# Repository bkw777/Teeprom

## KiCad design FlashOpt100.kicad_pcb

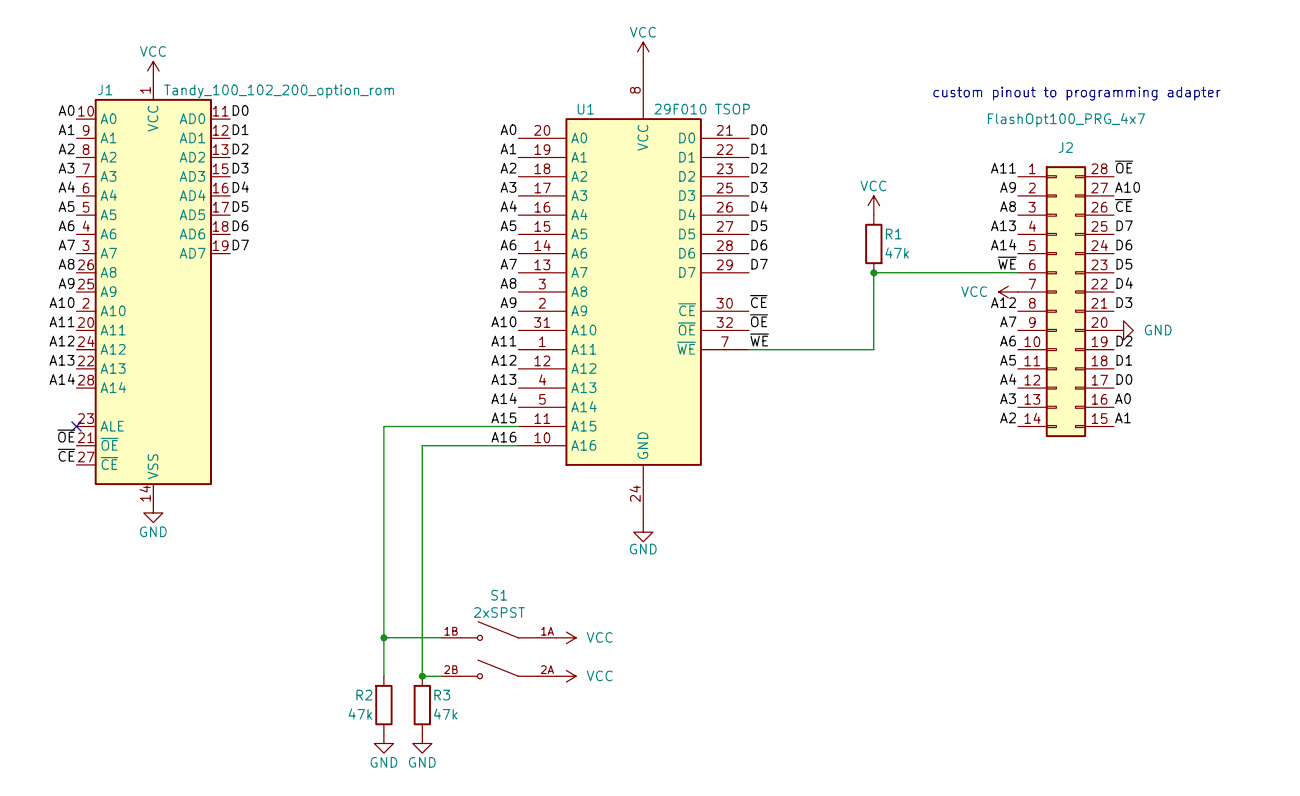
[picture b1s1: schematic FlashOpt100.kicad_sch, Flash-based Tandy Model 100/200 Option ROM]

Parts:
J1: Tandy_100_102_200_option_rom; Molex78802_PCB_28
J2: FlashOpt100_PRG_4x7; FlashOpt100_PRG_4x7_female_offset
R1, R2, R3: 47k; R_0805
S1: 2xSPST; SW_DS05-127-2-02BK-SMT-TR
U1: 29F010 TSOP; TSOP32-14mm

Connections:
/A0: J1.10 (A0), J2.16, U1.20 (A0)
/A1: J1.9 (A1), J2.15, U1.19 (A1)
/A2: J1.8 (A2), J2.14, U1.18 (A2)
/A3: J1.7 (A3), J2.13, U1.17 (A3)
/A4: J1.6 (A4), J2.12, U1.16 (A4)
/A5: J1.5 (A5), J2.11, U1.15 (A5)
/A6: J1.4 (A6), J2.10, U1.14 (A6)
/A7: J1.3 (A7), J2.9, U1.13 (A7)
/A8: J1.26 (A8), J2.3, U1.3 (A8)
/A9: J1.25 (A9), J2.2, U1.2 (A9)
/A10: J1.2 (A10), J2.27, U1.31 (A10)
/A11: J1.20 (A11), J2.1, U1.1 (A11)
/A12: J1.24 (A12), J2.8, U1.12 (A12)
/A13: J1.22 (A13), J2.4, U1.4 (A13)
/A14: J1.28 (A14), J2.5, U1.5 (A14)
/A15: R2.2, S1.1B, U1.11 (A15)
/A16: R3.2, S1.2B, U1.10 (A16)
/D0: J1.11 (AD0), J2.17, U1.21 (D0)
/D1: J1.12 (AD1), J2.18, U1.22 (D1)
/D2: J1.13 (AD2), J2.19, U1.23 (D2)
/D3: J1.15 (AD3), J2.21, U1.25 (D3)
/D4: J1.16 (AD4), J2.22, U1.26 (D4)
/D5: J1.17 (AD5), J2.23, U1.27 (D5)
/D6: J1.18 (AD6), J2.24, U1.28 (D6)
/D7: J1.19 (AD7), J2.25, U1.29 (D7)
/~CE: J1.27 (~CE), J2.26, U1.30 (~CE)
/~OE: J1.21 (~OE), J2.28, U1.32 (~OE)
/~WE: J2.6, R1.2, U1.7 (~WE)
GND: J1.14 (VSS), J2.20, R2.1, R3.1, U1.24 (GND)
VCC: J1.1 (VCC), J2.7, R1.1, S1.1A, S1.2A, U1.8 (VCC)

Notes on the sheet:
custom pinout to programming adapter

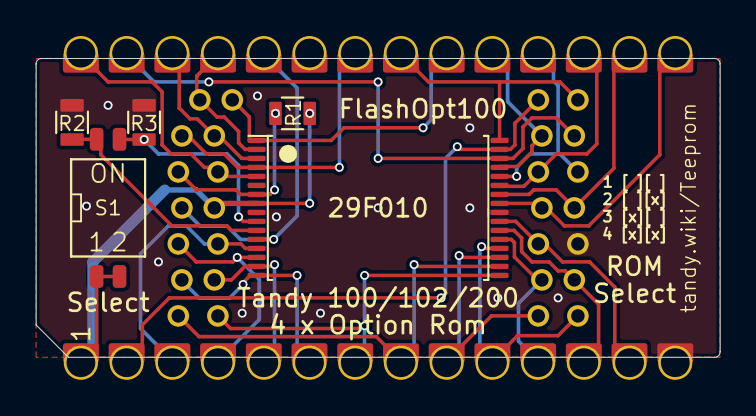
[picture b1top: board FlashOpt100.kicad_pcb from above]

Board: 2 copper layers, 38.0 x 16.6 mm, 7 parts (0 on the bottom side), 30 nets.

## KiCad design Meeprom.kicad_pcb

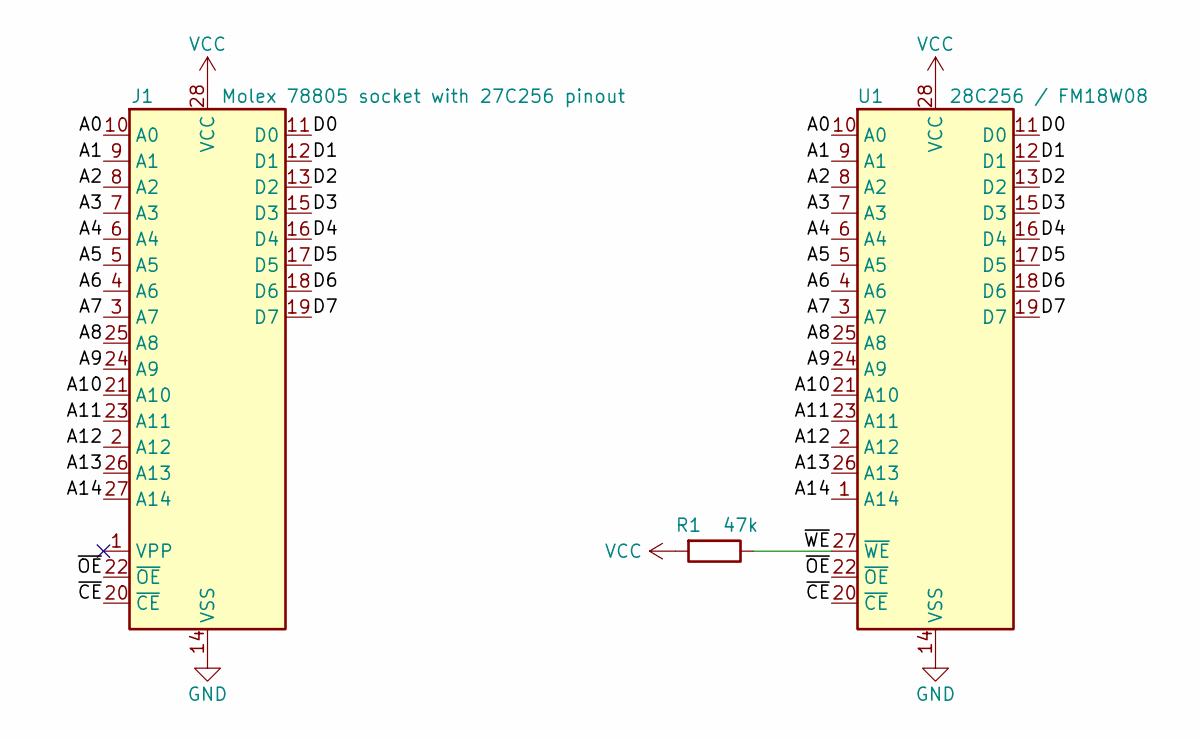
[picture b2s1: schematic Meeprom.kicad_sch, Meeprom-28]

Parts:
J1: Molex 78805 socket with 27C256 pinout; Molex78802_PCB_28
R1: 47k; R_0805
U1: 28C256 / FM18W08; SOIC-28W

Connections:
/A0: J1.10 (A0), U1.10 (A0)
/A1: J1.9 (A1), U1.9 (A1)
/A2: J1.8 (A2), U1.8 (A2)
/A3: J1.7 (A3), U1.7 (A3)
/A4: J1.6 (A4), U1.6 (A4)
/A5: J1.5 (A5), U1.5 (A5)
/A6: J1.4 (A6), U1.4 (A6)
/A7: J1.3 (A7), U1.3 (A7)
/A8: J1.25 (A8), U1.25 (A8)
/A9: J1.24 (A9), U1.24 (A9)
/A10: J1.21 (A10), U1.21 (A10)
/A11: J1.23 (A11), U1.23 (A11)
/A12: J1.2 (A12), U1.2 (A12)
/A13: J1.26 (A13), U1.26 (A13)
/A14: J1.27 (A14), U1.1 (A14)
/D0: J1.11 (D0), U1.11 (D0)
/D1: J1.12 (D1), U1.12 (D1)
/D2: J1.13 (D2), U1.13 (D2)
/D3: J1.15 (D3), U1.15 (D3)
/D4: J1.16 (D4), U1.16 (D4)
/D5: J1.17 (D5), U1.17 (D5)
/D6: J1.18 (D6), U1.18 (D6)
/D7: J1.19 (D7), U1.19 (D7)
/~CE: J1.20 (~CE), U1.20 (~CE)
/~OE: J1.22 (~OE), U1.22 (~OE)
/~WE: R1.1, U1.27 (~WE)
GND: J1.14 (VSS), U1.14 (VSS)
VCC: J1.28 (VCC), R1.2, U1.28 (VCC)

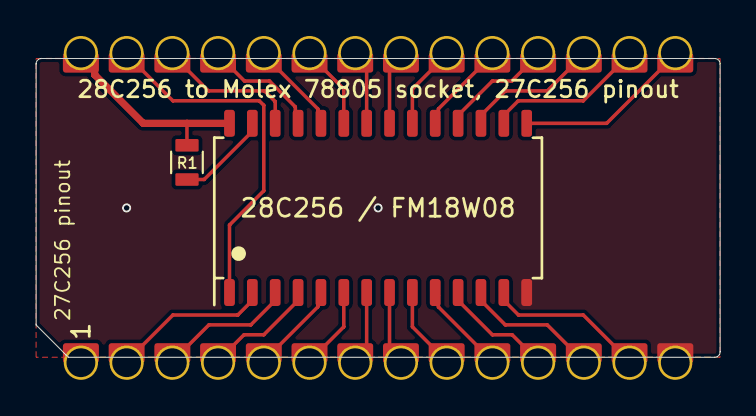
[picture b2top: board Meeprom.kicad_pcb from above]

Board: 2 copper layers, 38.0 x 16.6 mm, 3 parts (0 on the bottom side), 28 nets.

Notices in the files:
FlashOpt100.kicad_pcb:
CC-BY-SA
